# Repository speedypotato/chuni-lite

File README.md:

# chuni-lite
Slidy air towers for an arcade chuni slider without backplate.  Bare minimum docs because I don't expect too many people to have access to chuni cab sliders without backplates.

Current versions can be found at:
- CAD: chuni-lite\chunair-cad\airs\print\f1
- PCB: chuni-lite\chunair\chunair\chunair_v2\v2-1-2 & chuni-lite\chunair\chunair_core\v1

Note: I swapped the side the pads are on for chunair_core.  Oops.  Wires will go across the board for now, no biggie.  WS2811/WS2812B optional.

Slider needs:
- HiLetgo 2pcs DB9 Female Adapter RS232 to Terminal RS232 Serial to Terminal DB9 Connector Convert Adapter https://www.amazon.com/gp/product/B082F873KQ (technically just one)
- CQRobot 450 Pieces 2.54mm JST-XA JST Connector Kit. 2.54mm Pitch Female Pin Header, JST XA 2/3 / 4 Pin Housing JST Adapter Cable Connector Socket Male and Female, Crimp DIP Kit. https://www.amazon.com/gp/product/B085QMRHK6 (technically just a 3 & 4 pin).  3 pin needed pegs clipped.
- USB to VGA/RS-232 Male 9 PIN DB9 Serial Cable 2 FT WIN10/8.1/8/7 PERFECT VISION https://www.amazon.com/gp/product/B097Q5D64Q/ (or any other usb to serial cable)
- 12V 1A PSU minimum with matching female barrel jack that has the screw terminals https://www.amazon.com/gp/product/B091XSVV1Y/

Air towers need:
- 1x USB C Pro Micro x1
- IR LEDs https://www.amazon.com/gp/product/B01BVGIZGC/ and IR Photodiodes https://www.amazon.com/gp/product/B01BVGIZGM (chanzon ones seem pretty high quality) x6 of each(but they come in pack of 100)
- 150 ohm resistor x6
- 10k ohm resistor x6
- some ribbon wire https://www.ebay.com/itm/334199317464 100-Feet Flat Ribbon Cable Grey 50-Conductor 28 AWG Belden 2L28050 008H100
- 12x2mm magnets https://www.ebay.com/itm/391899288494 x10 (but they come in pack of 100)
- Rubber Feet https://www.mcmaster.com/8884T21 x4
- Adhesive Rubber Feet https://www.aliexpress.com/item/1005002618606773.html x4 (but they come in pack of 100)
- M3 Nuts x18
- M3x8 x4
- M4x16 https://www.mcmaster.com/91292A118 x4 (but they come in pack of 100)
- M3x15 flat head https://www.mcmaster.com/92125A103 x8 (but they come in pack of 100)
- M3x20 round head https://www.mcmaster.com/94500A266 x6 (but they come in pack of 100)
- 1 inch hinges https://www.amazon.com/gp/product/B07WJSTNC9 (MroMax 15PCS Door Hinge 1.14" x 0.71" x 0.02" Silver Tone Metal Iron Hinges Brushed Finish Suitable for Door Cabinet Jewelry Case Wooden Box) x2 (but pack of 15) - can try other hinges but holes may not align
- 3D printed parts + a mirrored set
- USB C cable
- Hot Glue & Super Glue
- Small zip ties x4

Can hand wire, or replace air_tower_top_1 3D print with chunair pcb.  chunair_core PCB also optional, but is there for ease of wiring(find a way to secure the pro micro if you don't use chunair_core)

Basic steps:
0. Wire up your slider's 12v and DB9.  Crimps recommended.  11" 4 wire recommended for 12v, 9" 3 wire for DB9.

1. Print parts.  Then print a mirrored set.  Glue magnets with super glue except for the one on slider which is inserted from the outside - glue that one in with hot glue.  Pay attention to the magnetic poles!!

2. Assemble slider_rail and air_tower with hinge, flat head screws, and nuts and insert into slider (double check orientation)

3. Glue leds/pds if you are using air_tower_top_1.  Wire according to the diagram in "ac chuni/wiring.png".  If you have PCB, solder resistors and leds/pds - 10K resistors are marked, the other 3 are 150 ohm resistors.  With PCB, recommended wire length is around 30", 9 wires for RGB, 8 for no RGB.  
3a. If you want RGB, add a 3 piece WS2812B LED strip in the middle and solder it up like the picture.

4. Shove unsoldered end of ribbon cable through the channel.
5. Screw air_tower_top_2 to the pcb or air_tower_top_1(depending on which you have) using rounded m3 heads while threading through air_tower.  Don't forget to put the printed bumper piece on one of the screws.

6. Solder to Pro Micro or chunair_core pcb depending on what you have.  Make sure you slide the slider_rail into the slider first before soldering.

7. Repeat steps 2-6 for the other side.

8. Add zip ties to core.  Use 4 m3x8 bolts and nuts to mount db9 and chunair_core to core.  Press fit 12v barrel connector and hot glue into place.

9. Thread M4 screws through rubber foot and slider to mount to slider.

10. Use existing M4 screws on the chunithm slider to mount core.  Zip tie down core & power cable
11. Flash firmware and test to make sure everything works.  Then add adhesive rubber feet on each bumper in addition to the bottom of the airs.

This work is licensed under a Creative Commons Attribution-NonCommercial-ShareAlike 4.0 International License.

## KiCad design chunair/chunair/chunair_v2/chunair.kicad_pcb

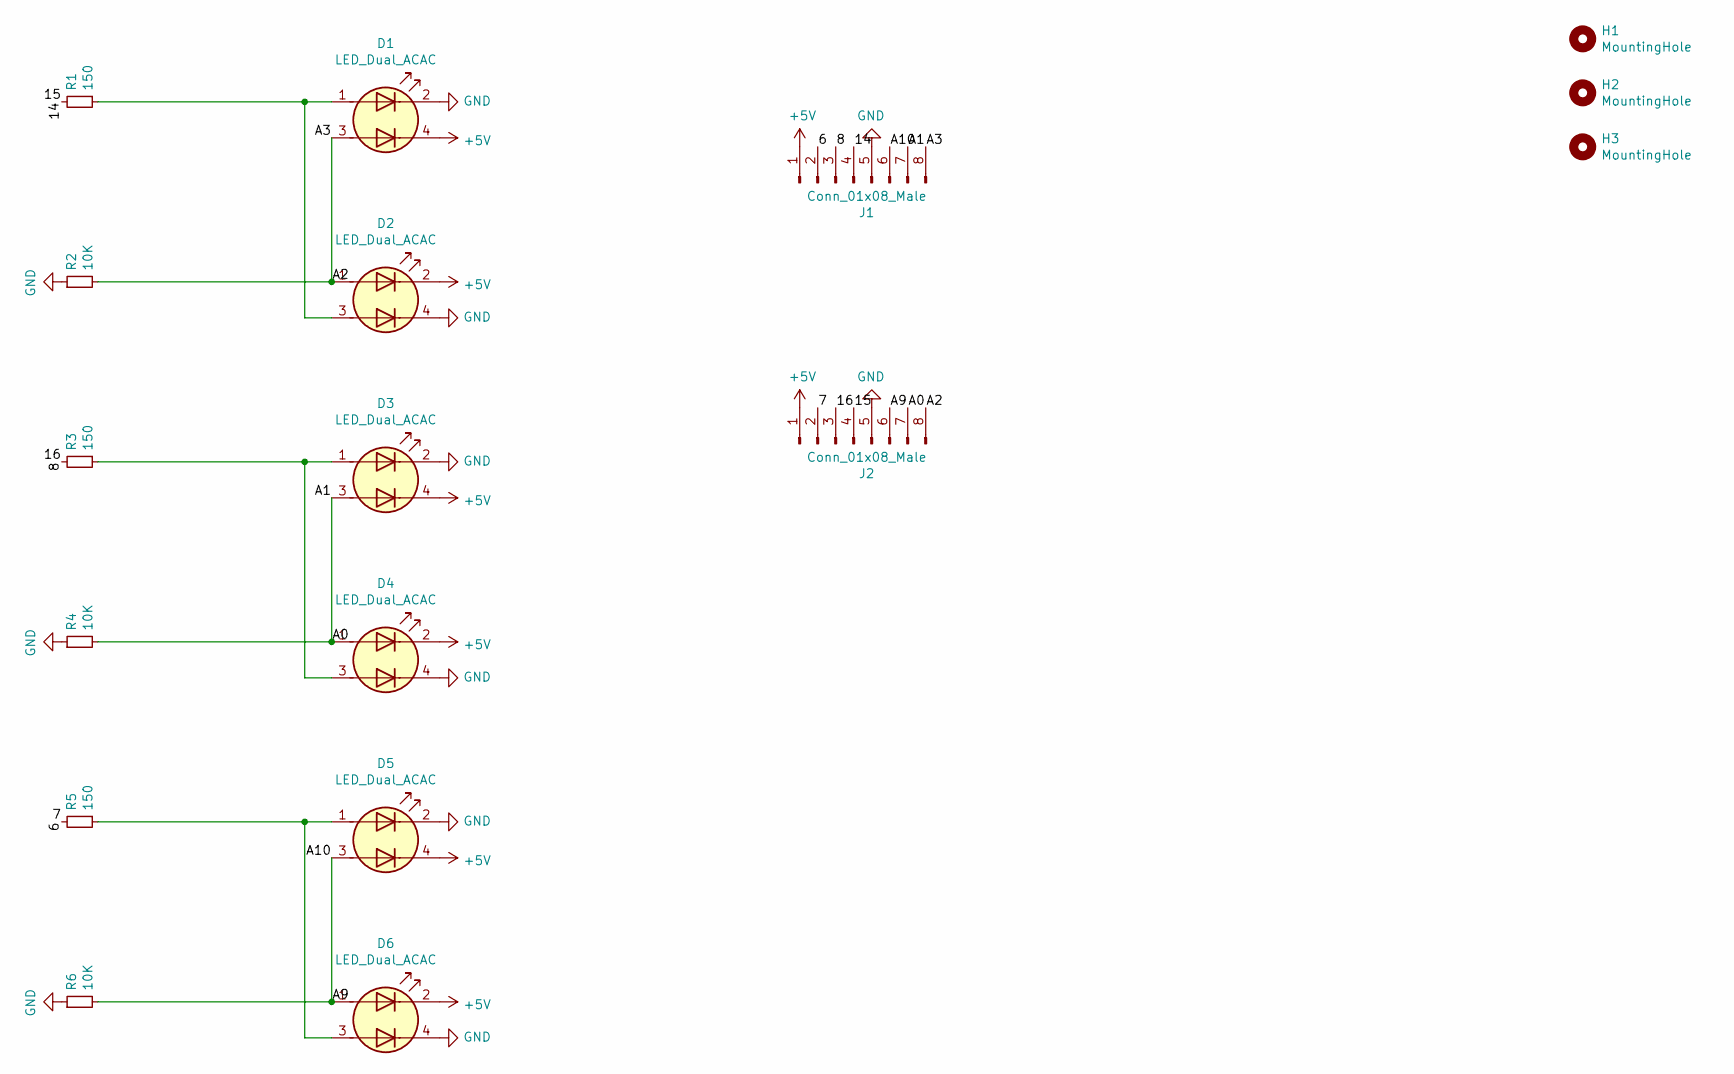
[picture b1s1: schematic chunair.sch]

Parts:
D1, D2, D3, D4, D5, D6: LED_Dual_ACAC; LED_D5.0mm_FlatTop
H1, H2, H3: MountingHole; MountingHole_3.2mm_M3
J1, J2: Conn_01x08_Male; SMD_8Pin
R1, R3, R5: 150; R_Axial_DIN0207_L6.3mm_D2.5mm_P7.62mm_Horizontal
R2, R4, R6: 10K; R_Axial_DIN0207_L6.3mm_D2.5mm_P7.62mm_Horizontal

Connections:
+5V: D1.4 (K2), D2.2 (K1), D3.4 (K2), D4.2 (K1), D5.4 (K2), D6.2 (K1), J1.1, J2.1
/6: J1.2, J2.2, R5.2
/14: J1.4, J2.4, R1.2
/16: J1.3, J2.3, R3.2
/A0: D3.3 (A2), D4.1 (A1), J1.7, J2.7, R4.2
/A2: D1.3 (A2), D2.1 (A1), J1.8, J2.8, R2.2
/A10: D5.3 (A2), D6.1 (A1), J1.6, J2.6, R6.2
GND: D1.2 (K1), D2.4 (K2), D3.2 (K1), D4.4 (K2), D5.2 (K1), D6.4 (K2), J1.5, J2.5, R2.1, R4.1, R6.1
unnamed: D1.1 (A1), D2.3 (A2), R1.1
unnamed: D3.1 (A1), D4.3 (A2), R3.1
unnamed: D5.1 (A1), D6.3 (A2), R5.1

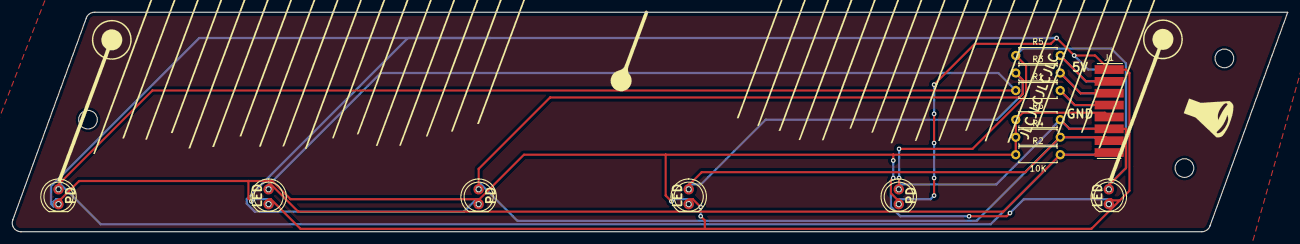
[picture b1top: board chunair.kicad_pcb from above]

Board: 2 copper layers, 218.6 x 37.6 mm, 17 parts (1 on the bottom side), 11 nets.

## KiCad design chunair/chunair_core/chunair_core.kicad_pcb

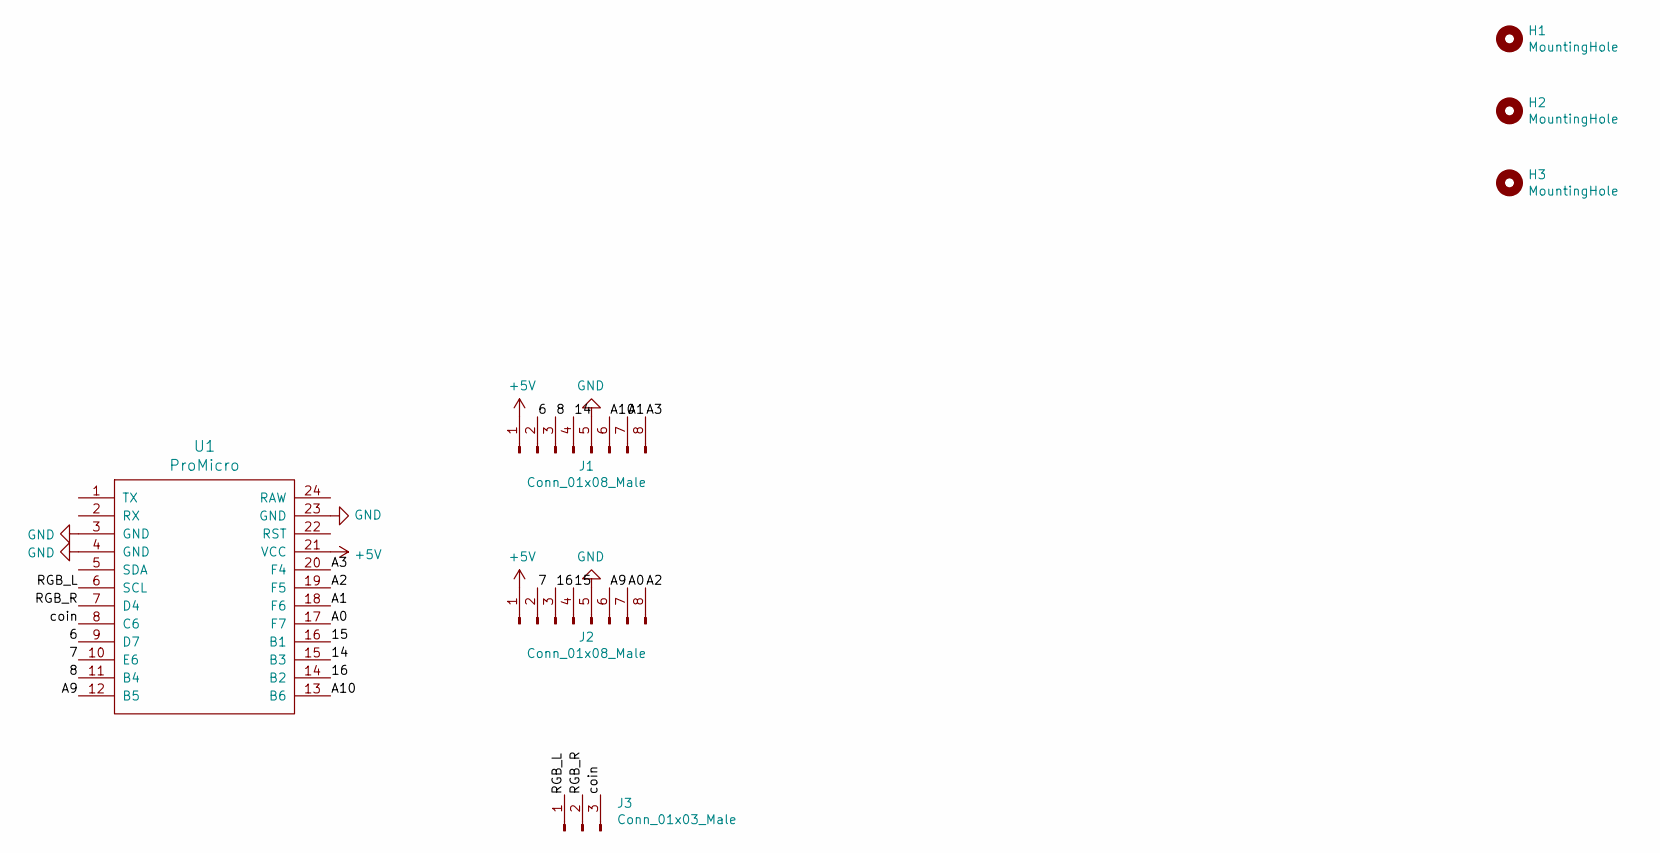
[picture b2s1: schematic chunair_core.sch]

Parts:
H1, H2, H3: MountingHole; MountingHole_3.2mm_M3
J1, J2: Conn_01x08_Male; SMD_8Pin
J3: Conn_01x03_Male; SMD_3Pin
U1: ProMicro; ProMicro-EnforcedTop

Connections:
+5V: J1.1, J2.1, U1.21 (VCC)
/6: J1.2, U1.9 (D7)
/7: J2.2, U1.10 (E6)
/8: J1.3, U1.11 (B4)
/14: J1.4, U1.15 (B3)
/15: J2.4, U1.16 (B1)
/16: J2.3, U1.14 (B2)
/A0: J2.7, U1.17 (F7)
/A1: J1.7, U1.18 (F6)
/A2: J2.8, U1.19 (F5)
/A3: J1.8, U1.20 (F4)
/A9: J2.6, U1.12 (B5)
/A10: J1.6, U1.13 (B6)
/RGB_L: J3.1, U1.6 (SCL)
/RGB_R: J3.2, U1.7 (D4)
/coin: J3.3, U1.8 (C6)
GND: J1.5, J2.5, U1.3 (GND), U1.4 (GND), U1.23 (GND)

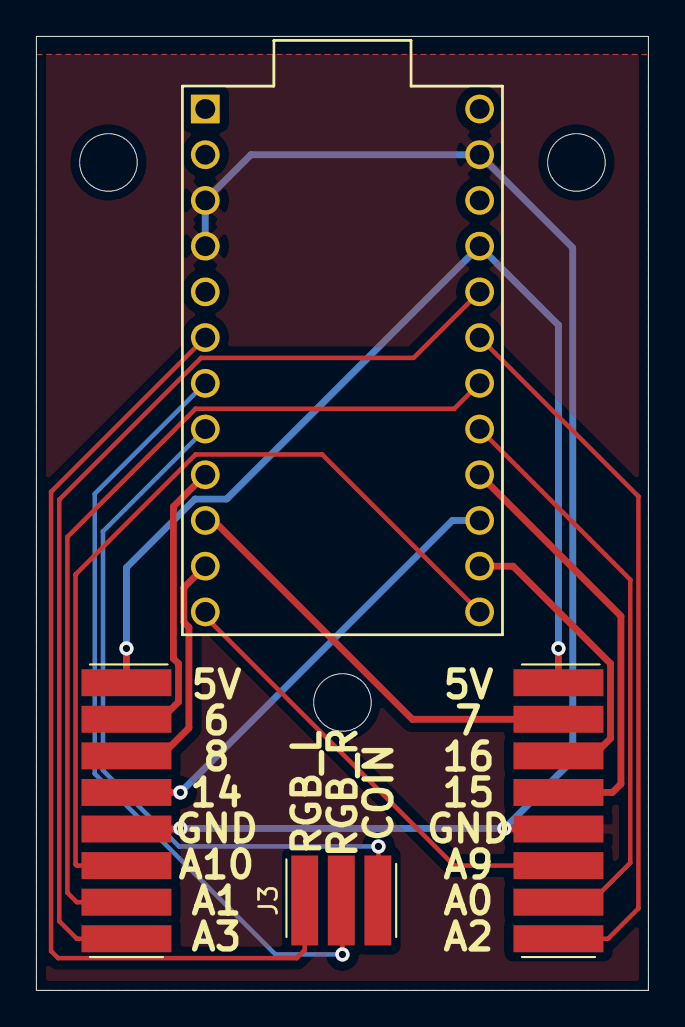
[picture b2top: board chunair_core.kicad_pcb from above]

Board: 2 copper layers, 34.0 x 53.0 mm, 7 parts (0 on the bottom side), 17 nets.

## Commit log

2022-02-10 wip, todo air_2
2022-02-23 v1.0 | Handwired Proto
2022-02-25 Added firmware and air pcb
2022-02-26 Added basic core breakout pcb, minor firmware updates
2022-02-26 basic instructions and parts list
2022-02-28 v2.0 | Added first ordered revision of PCBs
2022-03-18 minor fw updates for rgb
2022-03-19 Working serial RGB, but GRB is incorrect
2022-03-22 v1.0 | Final version and docs, pictures later
2022-03-23 Pictures
2022-04-07 Added optional clips for air towers
2022-08-01 Update code from WS2811 -> WS2812B
2022-08-01 Umigiri default bindings
